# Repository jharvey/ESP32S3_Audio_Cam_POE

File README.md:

# ESP32S3_Audio_Cam_POE

This is a PCB layout for ESP32S3 with OV2640 / OV5640 camera. It was designed in KiCad 9 and converted to KiCad 10 (10.0.8); the files no longer open in KiCad 9.
The board's major features include:
* Camera.
* 2 way audio.
* Hardwired Ethernet including POE.
* Camera pan / tilt servos and lamp control.
* record to SD card.
* misc outputs to drive misc motors or similar outputs. 
* Battery powered option with Li-ion type of battery. 
* Stream video to NVR recording station. 

## Firmware
Firmware found here https://github.com/jharvey/ESP32-CAM_MJPEG2SD

Changes up to version 0.1:
* Initial layout
* Converted to KiCad 10.
* Removed the Medium and Smaller cost-reduction variants.

## Purpose

The layout design intent is to make a hardwired intercom system which includes options for camera, making a near equivalent of a doorbell camera. Hardwired means it's not susceptible to RF jamming, or similar attacks. It can be battery powered at the ethernet switch source so it can handle power outages. Lighting controls allow night time spot light, and day time spot light controls. Pan, Tilt, Rotate could potentially allow a laser pointer to distract bad players if things go bump in the night. 

## Installation
Clone with the JLCPCB library submodule, which the symbol and footprint tables point to:

```
git clone --recurse-submodules https://github.com/jharvey/ESP32S3_Audio_Cam_POE.git
```

All JLCPCB symbols, footprints and 3D models resolve from this submodule, so you do not need the JLCPCB library installed through the KiCad Plugin and Content Manager. Other 3D models use KiCad's standard `${KICAD10_3DMODEL_DIR}` library.

On Windows, if the submodule fails with "Filename too long" or "'$GIT_DIR' too big", enable long paths first (`git config --global core.longpaths true`) or clone to a shorter folder.

TBD currently has not had its first spin. TBD

## Layout status
The `single-sided` branch puts every assembled part on the top of a 4-layer board. Routing is in progress: see
[Docs/single_sided_layout.md](Docs/single_sided_layout.md) for the layout and
[Docs/routing_handoff.md](Docs/routing_handoff.md) for what is routed, what is open and how to continue.

## 3D case
See 3D case found here
TBD create file in OnShape and post link here. TBD

## 3D pictures from KICAD
<div align="center">

</div>

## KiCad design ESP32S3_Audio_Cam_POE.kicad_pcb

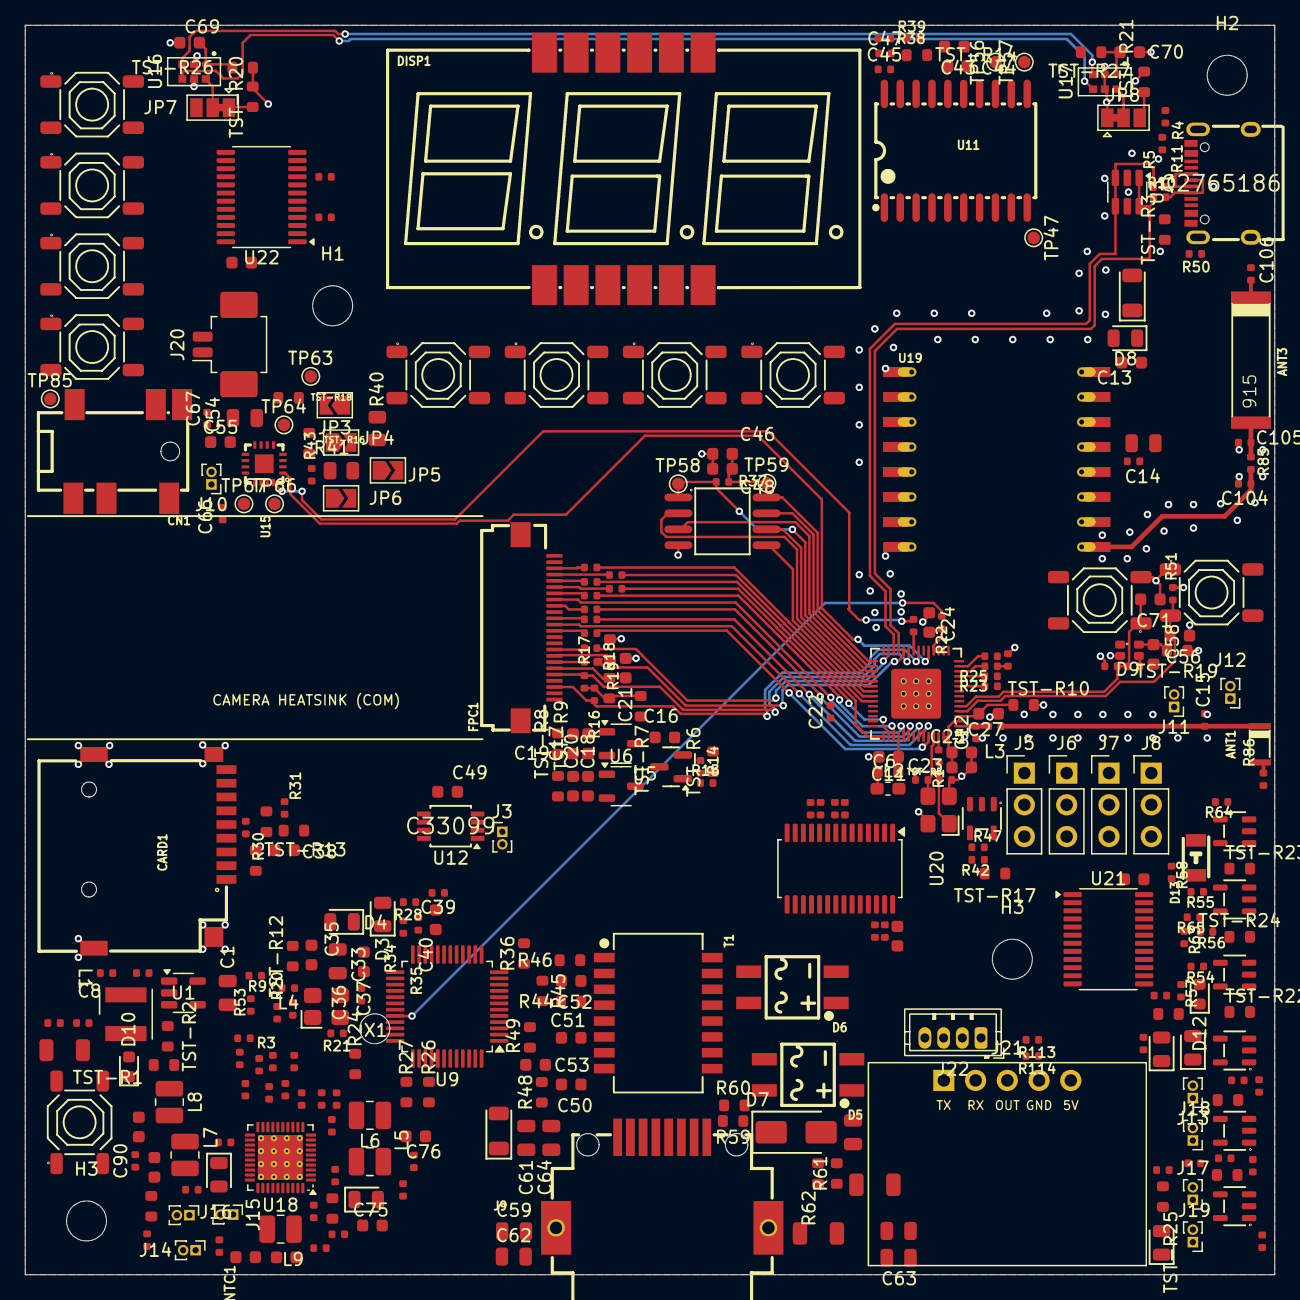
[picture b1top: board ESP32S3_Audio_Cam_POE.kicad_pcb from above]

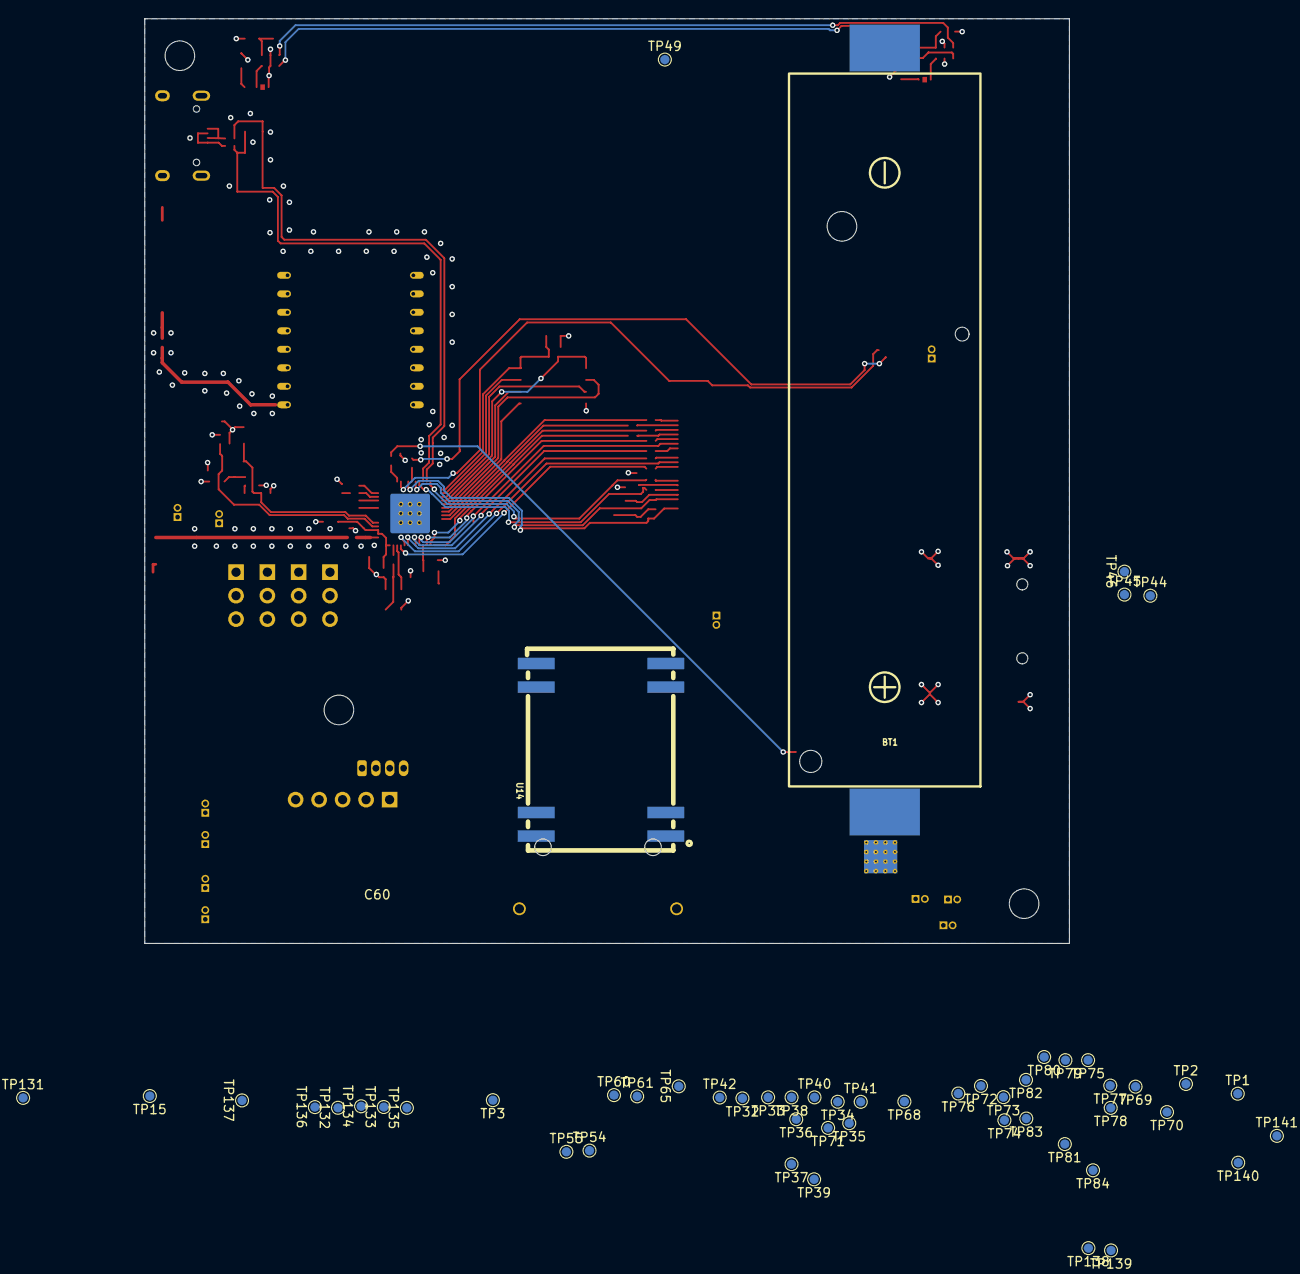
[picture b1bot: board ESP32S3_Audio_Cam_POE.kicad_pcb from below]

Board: 4 copper layers, 100.0 x 100.0 mm, 384 parts (54 on the bottom side), 275 nets.

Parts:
ANT1: KH-3216-H0209; ANT-SMD_L3.2-W1.6-KH-3216F245C04
ANT3: H2U646MHLQ0200; ANT-SMD_H2U646MHLQ0200
BOOT1: Tactile Button, 160gf; SW-SMD_4P-L5.1-W5.1-P3.70-LS6.5-TL-2
BT1: BH-18650-B1BA002; BATTERY-SMD_18650-1S-L77.1-W20.7-1
C1: 4.7uF; C_0805
C3, C6, C33, C34, C106: 10pF; C_0402
C8, C14, C74: 10uF; C_0402
C11, C13, C19, C20, C21, C24, C25, C27, C35, C37, C38, C44, C46, C49, C55, C56, C58, C69, C70, C71, C100, C108, C109: 100nF; C_0603
C12, C105: 3.3pF; C_0402
C15: 1pF; C_0402
C16, C17, C18, C23, C43, C48: 1uF; C_0603
C22: 15pF; C_0402
C36, C54, C61, C103: 10uF; C_0805
C39: 10nF; C_0402
C40: 4.7uF; C_0603
C45, C47: 100pF; C_0402
C50, C51: 6.8nF; C_0603
C52, C53: 220nF; C_0603
C59, C60, C62, C63, C107: 100nF; C_0805
C64: 22uF; C_0805
C65, C68: 1nF; C_1206
C66, C67: 220pF; C_0402
C73, C88, C90, C91, C92, C93, C94: 1uF; C_0402
C75, C76, C77, C78, C95, C97: 22uF; C_0603
C79, C80, C81, C82, C83, C84, C85, C86, C87, C96: 2.2uF; C_0402
C89: 4.7uF; C_0402
C104: 4.7pF; C_0402
CARD1: TF PUSH; TF-PUSH-SD-CARD_C393941
CN1: PJ-316C-6A; SMD_3.5mm_Audio_Connectors_(Headphones)_C707223
D1, D11: DSK24; D_SOD-123FL
D3: Yellow; D_0805
D4, D8, D15, D16, D17, D18: Green; D_0805
D5, D6: MB6S; MB6S-C82584
D7: SMAJ58A; D_SMA
D9: WS2812B; LED-SMD_4P-L1.6-W1.5_XL-1615RGBC-WS2812B
D10: Red; D_0603
D12: White; D_0603
D13: IR; IR-LED_C131280
D14: Blue; D_0805
DISP1: SLS0563DBA1GD; 3x7-seg_LED-RED_C2913084
FPC1: AFC01-S24FCC-00; OV2640_connector_AFC01-S24FCC-00
H1, H2, H3, H3#2: M3; MountingHole_3.2mm_M3
J1: Connector, USB-TYPE-C-16P; USB-C-SMD_TYPE-C-16PIN-2MD-073
J3, J10, J11, J12, J13, J14, J15, J16, J17, J18, J19: Conn_01x02; PinHeader_1x02_P1.00mm_Vertical
J5, J6, J7, J8: Conn_01x03; PinHeader_1x03_P2.54mm_Vertical
J9: HC-RJ45-055-4_8P8C_Shielded; HC-RJ45-055-4_C3000211
J20: 53261-0271; Molex_PicoBlade_53261-0271_1x02-1MP_P1.25mm_Horizontal
J21: HLK-LD2410C
J22: HLK-LD2450 cable; JST_ZH_B4B-ZR_1x04_P1.50mm_Vertical
JP3, JP4, JP5, JP6: SolderJumper_2_Open; SolderJumper-2_P1.3mm_Open_TrianglePad1.0x1.5mm
JP7, JP8: SolderJumper_3_Bridged12; SolderJumper-3_P1.3mm_Bridged12_Pad1.0x1.5mm
L1: 2.2uH; L_Wurth_WE-LQSH-4020
L2: 2nH; L_0603_1608Metric_Pad1.05x0.95mm_HandSolder
L3, L4: 3.9nH,300mA; L_0402
L5, L6, L7, L8, L9: 1uH,3.3A; L_1008_2520Metric
NTC1: NTC; R_0402
PB1, PB2, PB3, PB4, PB5, PB7, PB10, PB11, PB12: Tactile Button, 160gf; SW-SMD_4P-L5.1-W5.1-P3.70-LS6.5-TL-2
Q1: AO3401A; Q_SOT-23
Q2, Q3, Q4, Q5, Q6, Q7, Q8: SY6288AAAC; SOT-23-5_L3.0-W1.7-P0.95-LS2.8-BL
R1, R3, R22, R23, R25: 22Ω; R_0402
R4, R5: 5.1kΩ; R_0402
R8, R9, R37, R42, R54, R55, R56, R79, R82, R101: 100kΩ; R_0402
R10, R11, R88, R89, R90, R91, R92, R93, R94, R95, R96, R97, R98, R99, R100, R110: 33Ω; R_0402
R14: 10MΩ; R_0402
R15, R20, R43: 1MΩ; R_0402
R16, R17, R28, R30, R31, R38, R39, R50, R51, R53, R64, R65, R67, R75, R78, R81, R84, R109: 10kΩ; R_0402
R18, R19: 10kΩ; R_0603
R21, R85, R86, R113, R114: 0Ω; R_0402
R24, R26, R27: 20Ω; R_0603
R29, R32, R36: 12kΩ; R_0603
R34, R35: 680Ω; R_0402
R40, R41: 100kΩ; R_0805
R44, R45, R46: 47Ω; R_0603
R47, R57, R58, R63, R66, R77, R80, R83, R111, R112: 1kΩ; R_0402
R48, R49: 82Ω; R_0603
R59, R60, R61, R62: 75Ω; R_0603
R74, R76: 220kΩ; R_0402
R102, R103, R104, R105, R106, R107: 4.7kΩ; R_0402
R108: 0Ω; R_1206
RST2: Tactile Button, 160gf; SW-SMD_4P-L5.1-W5.1-P3.70-LS6.5-TL-2
T1: H1102NLT; H1102NLT_C18584
TP1, TP2, TP3, TP15, TP32, TP33, TP34, TP35, TP36, TP37, TP38, TP39, TP40, TP41, TP42, TP44, TP45, TP46, TP47, TP49, TP54, TP55, TP56, TP57, TP58, TP59, TP60, TP61, TP63, TP64, TP65, TP66, TP67, TP68, TP69, TP70, TP71, TP72, TP73, TP74, TP75, TP76, TP77, TP78, TP79, TP80, TP81, TP82, TP83, TP84, TP85, TP131, TP132, TP133, TP134, TP135, TP136, TP137, TP138, TP139, TP140, TP141: TestPoint; TestPoint_Pad_D1.0mm
TST-R1, TST-R2, TST-R3, TST-R5, TST-R6, TST-R7, TST-R8, TST-R9, TST-R10, TST-R12, TST-R13, TST-R14, TST-R16, TST-R17, TST-R18, TST-R19, TST-R20, TST-R21, TST-R22, TST-R23, TST-R24, TST-R25, TST-R26, TST-R27, TST-R28, TST-R29, TST-R30, TST-R31, TST-R32: 0Ω; R_0603
U1: TLV62568DBVR; SOT-23-5
U3: USBLC6-2SC6; SOT-23-6
U5: XC6206-1.5NR; SOT-23-3
U6: XC6206-2.8V; SOT-23-3
U7: ESP32-S3; QFN-56-1EP_7x7mm_P0.4mm_EP4x4mm_ThermalVias
U9: W5500; LQFP-48_7x7mm_P0.5mm
U11: TM1637; digital tube drivers_c2962580
U12: LM75BDP,118; TSSOP-8_3x3mm_P0.65mm
U13: W25Q128JVSIQ; SOIC-8_L5.3-W5.3-P1.27-LS8.0-BL
U14: DP9900M-5V; DP9900M_C5380106
U15: MAX98357AETE+T; MAX98357AETE+T_C910544
U16, U17: MSM261DGT003; LGA-6_2.0x4.0mm_MSM261DGT003
U18: AXP2101; QFN-40-1EP_5x5mm_P0.4mm_EP3.6x3.6mm_ThermalVias
U19: DL-RFM95-915M; RFM69HCW
U20: PCA9685PW; TSSOP-28_4.4x9.7mm_P0.65mm
U21, U22: TCA9555PWR; TSSOP-24_4.4x7.8mm_P0.65mm
X1: X322525MOB4SI; OSC-SMD_4P-L3.2-W2.5-BL
Y1: 40MHz, 15pF; OSC-SMD_4P-L3.2-W2.5-BL_SIT8008BI

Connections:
+1V5: FPC1.10 (10_1V2), TST-R8.2
+2V8: FPC1.4 (4_2V8), FPC1.11 (11_2V8), TST-R9.2
+3V3: C13.2, C14.1, C49.2, C100.1, C103.1, C108.1, C109.2, D3.2, D4.2, L2.2, R51.2, R53.2, R102.1, R103.1, R104.1, R105.1, R106.1, R107.1, R109.2, TST-R2.2, TST-R6.2, TST-R7.1, TST-R10.2, TST-R12.2, TST-R13.2, TST-R14.2, TST-R19.2, TST-R20.2, TST-R21.2, TST-R26.2, TST-R27.2, TST-R29.2, U12.8 (+Vs), U19.5 (VDD), U20.28 (VDD), U21.24 (VCC), U22.21 (A0), U22.24 (VCC)
+3V3A: C36.2, C37.2, L4.1, R44.2, R45.2, R46.2, U9.4 (AVDD), U9.8 (AVDD), U9.11 (AVDD), U9.15 (AVDD), U9.17 (AVDD), U9.21 (AVDD), U9.28 (VDD)
+3V3_RF: C11.2, TST-R5.1, U7.46 (VDD3P3_CPU)
/3V3-U16: C69.1, TST-R26.1, U16.1 (VDD)
/3V3-U17: C70.1, TST-R27.1, U17.1 (VDD)
/7SEG.GRID1: DISP1.12 (DIG1), U11.15 (GRID1)
/7SEG.GRID2: DISP1.8 (DIG2), U11.14 (GRID2)
/7SEG.GRID3: DISP1.7 (DIG3), U11.13 (GRID3)
/7SEG.SEG1: DISP1.9 (A), U11.2 (SEG1/KS1)
/7SEG.SEG2: DISP1.5 (B), U11.3 (SEG2/KS2)
/7SEG.SEG3: DISP1.4 (C), U11.4 (SEG3/KS3)
/7SEG.SEG4: DISP1.3 (D), U11.5 (SEG4/KS4)
/7SEG.SEG5: DISP1.1 (E), U11.6 (SEG5/KS5)
/7SEG.SEG6: DISP1.10 (F), U11.7 (SEG6/KS6)
/7SEG.SEG7: DISP1.2 (G), U11.8 (SEG7/KS7)
/7SEG.SEG8: DISP1.6 (DP), U11.9 (SEG8/KS8)
/BTN.DOWN: PB5.4 (D), U22.7 (P03)
/BTN.MODE: PB2.4 (D), U22.5 (P01)
/BTN.OFFICE: R112.1, U22.9 (P05)
/BTN.OFFICE_SW: PB7.4 (D), R112.2
/BTN.TALK1: R111.1, U22.4 (P00)
/BTN.TALK1_SW: PB1.4 (D), R111.2
/BTN.TALK10: PB10.4 (D), U22.13 (P10)
/BTN.TALK11: PB11.4 (D), U22.14 (P11)
/BTN.TALK12: PB12.4 (D), U22.15 (P12)
/BTN.UP: PB4.4 (D), U22.6 (P02)
/CAM.D0: R92.1, U7.44 (MTCK)
/CAM.D1: R94.1, U7.37 (SPICLK_P)
/CAM.D2: R95.1, U7.36 (SPICLK_N)
/CAM.D3: R93.1, U7.43 (GPIO38)
/CAM.D4: R91.1, U7.45 (MTDO)
/CAM.D5: R90.1, U7.48 (MTMS)
/CAM.D6: R89.1, U7.50 (U0RXD)
/CAM.D7: R88.1, U7.52 (GPIO46)
/CAM.HREF: R98.1, U7.27 (GPIO21)
/CAM.MCLK: FPC1.13 (13_MCLK), U7.51 (GPIO45)
/CAM.PCLK: C22.2, FPC1.17 (17_PCLK), U7.47 (MTDI)
/CAM.PWDN: FPC1.8 (8_PWDN), R19.2
/CAM.PWR: R15.2, U21.8 (P04)
/CAM.RST: C21.2, FPC1.6 (6_RST), R18.2
/CAM.SCL: FPC1.5 (5_SCL-SIO-CLK), R17.2, U7.23 (GPIO17)
/CAM.SDA: FPC1.3 (3_SDA-SIO-DAT), R16.2, U7.21 (XTAL_32K_P)
/CAM.VSYNC: R97.1, U7.24 (GPIO18)
/CHIP_BOOT: BOOT1.1 (A), C71.2, R109.1, R110.1, U7.5 (GPIO0)
/CHIP_PU: C56.2, R51.1, RST2.3 (C), U7.4 (CHIP_PU)
/CK_XTAL1: R21.2, U9.30 (XI/CLKIN)
/CK_XTAL2: C33.1, R20.1, U9.31 (XO), X1.1 (OSC)
/ESP.I2S.WS: R100.1, U7.13 (GPIO8)
/ESP.MIC.SCK: R96.1, U7.22 (XTAL_32K_N)
/ESP.MIC.SD: R99.1, U7.12 (GPIO7)
/ETH.CS: R22.1, U7.18 (GPIO13)
/ETH.INT_EXP: R26.1, U21.7 (P03)
/ETH.MISO: R24.1, U7.10 (GPIO5), U19.10 (MISO)
/ETH.MOSI: R25.1, U7.11 (GPIO6), U19.11 (MOSI)
/ETH.RST_EXP: R27.1, U21.6 (P02)
/ETH.SCLK: R23.1, U7.9 (GPIO4), U19.12 (SCK)
/EXP.INT: U21.1 (~INT), U22.1 (~INT)
/FGND1: C59.2, C60.1, C62.2, C63.1, C65.1, J9.9 (SH), J9.10 (SH)
/FLASH_QSPI_CLK: U7.33 (SPICLK), U13.6 (CLK)
/FLASH_QSPI_DI: U7.35 (SPID), U13.5 (DI)
/FLASH_QSPI_DO: U7.34 (SPIQ), U13.2 (DO)
/FLASH_QSPI_nCS: R37.1, TP58.1 (1_1), U7.32 (SPICS0), U13.1 (CS#)
/FLASH_QSPI_nH: U7.30 (SPIHD), U13.7 (IO3)
/FLASH_QSPI_nWP: U7.31 (SPIWP), U13.3 (IO2)
/FLT.IR: Q4.3 (OCB), U21.14 (P11)
/FLT.M1: Q6.3 (OCB), U21.16 (P13)
/FLT.M2: Q7.3 (OCB), U21.17 (P14)
/FLT.M3: Q8.3 (OCB), U21.18 (P15)
/FLT.OTH: Q5.3 (OCB), U21.15 (P12)
/FLT.RC: Q2.3 (OCB), U21.19 (P16)
/FLT.WH: Q3.3 (OCB), U21.13 (P10)
/I2C.SCL: J3.1, R102.2, U7.49 (U0TXD), U12.2 (SCL), U18.39 (SCK), U20.26 (SCL), U21.22 (SCL), U22.22 (SCL)
/I2C.SDA: J3.2, R103.2, U7.17 (GPIO12), U12.1 (SDA), U18.40 (SDA), U20.27 (SDA), U21.23 (SDA), U22.23 (SDA)
/I2S.SCK: R96.2, U15.16 (BCLK)
/I2S.WS: R100.2, U15.14 (LRCLK)
/LED.DIN: D9.4 (DIN), R110.2
/LED.IR: R58.2, U20.21 (LED14)
/LED.OTH: R63.2, U20.19 (LED12)
/LED.VDD: C58.2, D9.2 (VDD), TST-R19.1
/LED.WH: R57.2, U20.18 (LED11)
/LORA1: C104.1, R85.1, U19.1 (ANT)
/LORA1-ANT: ANT3.1 (ANT), C105.1, R85.2
/LORA_CS: U7.16 (GPIO11), U19.13 (NSS)
/LORA_IRQ: U19.6 (DIO0), U22.17 (P14)
/LORA_RST: U19.14 (RESET), U21.9 (P05)
/MIC.CLK: U7.14 (GPIO9), U16.4 (CLK), U17.4 (CLK)
/MIC.L: JP8.2 (C), U17.6 (L/R)
/MIC.R: JP7.2 (C), U16.6 (L/R)
/MIC.SD: R99.2, R101.1, U16.3 (DATA), U17.3 (DATA)
/MISC.OUT1: R77.2, U20.15 (LED8)
/MISC.OUT2: R80.2, U20.16 (LED9)
/MISC.OUT3: R83.2, U20.17 (LED10)
/OSC_IN: R1.2, U7.54 (XTAL_P)
/OSC_OUT: C6.1, U7.53 (XTAL_N), Y1.3 (OSC)
/PMU.IRQ: U18.38 (IRQ), U21.5 (P01)
/PMU.Va1: C79.2, U18.18 (ALDO1)
/PMU.Va2: C82.2, U18.19 (ALDO2)
/PMU.Va3: C80.2, U18.16 (ALDO3)
/PMU.Va4: C81.2, U18.15 (ALDO4)
/PMU.Vb1: C84.2, U18.12 (BLDO1)
/PMU.Vb2: C85.2, U18.14 (BLDO2)
/PMU.Vcpu: C86.2, U18.10 (CPULDOS)
/PMU.Vd1: C83.2, U18.20 (DLDO1/DC1SW)
/PMU.Vd2: C87.2, U18.11 (DLDO2/DC4SW)
/PMU.Vo1: C78.2, L8.1, TST-R29.1, U18.22 (LX1)
/PMU.Vo2: C77.2, L7.1, U18.26 (FB2)
/PMU.Vo3: C75.2, L5.1, U18.4 (FB3)
/PMU.Vo4: C76.2, L6.1, U18.8 (LX4)
/PMU.Vref: C73.2, U18.2 (VREF)
/PMU.Vsys: C88.2, C89.2, C91.2, C92.2, C93.2, C94.2, R66.2, R67.2, U18.6 (VIN3), U18.7 (VIN4), U18.13 (BLDOIN), U18.17 (ALDOIN), U18.23 (VIN1), U18.24 (VIN2), U18.34 (VSYS), U18.36 (VMID)
/POE_5V: C61.1, C64.1, D11.2, U14.1 (+VDC), U14.2 (+VDC)
/PWM.OE: U20.23 (~OE), U21.4 (P00)
/RADAR.OUT: J21.3, U22.16 (P13)
/RADAR.TX: J22.3, R113.1, U7.15 (GPIO10)
/RC.OTHR: J8.1, R107.2, U20.11 (LED5)
/RC.PAN: J5.1, R104.2, U20.7 (LED1)
/RC.PWR: R47.2, U20.22 (LED15)
/RC.ROT: J7.1, R106.2, U20.10 (LED4)
/RC.TILT: J6.1, R105.2, U20.8 (LED2)
/RC.VDD: J5.2, J6.2, J7.2, J8.2, Q2.1 (OUT)
/RF1: C12.1, L3.1, U7.1 (LNA_IN)
/RF1-ANT: ANT1.1 (ANT), C15.1, L3.2
/SD.CLK: CARD1.5 (CLX), R31.2, U7.7 (GPIO2)
/SD.CS: CARD1.2 (CD/DAT3), R29.2
/SD.MISO: CARD1.7 (DAT0), R32.2, U7.6 (GPIO1)
/SD.MOSI: CARD1.3 (CMD), R30.2, U7.8 (GPIO3)
/SPK.DIN: U7.19 (GPIO14), U15.1 (DIN)
/SPK.MIC: CN1.4, TP85.1 (1_1)
/SPK.MODE: R43.2, U15.4 (SD_MODE#)
/SPK.OutN: C66.2, CN1.1, J10.2, J20.2, U15.10 (OUTN)
/SPK.OutP: C67.1, CN1.2, CN1.3, U15.9 (OUTP)
/SPK.OutPS: CN1.5, CN1.6, J10.1, J20.1
/TM.CLK: C45.2, R38.1, U11.18 (CLK), U21.10 (P06)
/TM.DIO: C47.2, R39.1, U11.17 (DIO), U21.11 (P07)
/USB_CC1: J1.A5 (CC1), R4.1
/USB_CC2: J1.B5 (CC2), R5.1
/USB_D+: R11.2, U3.3 (I/O2), U3.4 (I/O2), U7.26 (GPIO20/USB_D+)
/USB_D-: R10.2, U3.1 (I/O1), U3.6 (I/O1), U7.25 (GPIO19/USB_D-)
/USB_PRT_D+: J1.A6 (D+), J1.B6 (D+), R11.1
/USB_PRT_D-: J1.A7 (D-), J1.B7 (D-), R10.1
/VDCDC5: C95.2, C97.2, L9.1, U18.32 (GPIO1/FB5/RTC/LDO2)
/W_BR_N: C107.2, D5.2 (-), D6.2 (-), D7.2, U14.7 (VIN-), U14.8 (VIN-)
/W_BR_P: C107.1, D5.1 (+), D6.1 (+), D7.1, U14.5 (VIN+), U14.6 (VIN+)
/W_RD_N: J9.6, T1.9
/W_RD_OUT_N: C50.2, R48.1, U9.5 (RXN)
/W_RD_OUT_P: C51.2, R49.1, U9.6 (RXP)
/W_RD_P: J9.3, T1.11
/W_RXCM: D6.4, T1.10
/W_TD_N: J9.2, T1.14
/W_TD_OUT_N: R44.1, T1.3, U9.1 (TXN)
/W_TD_OUT_P: R46.1, T1.1, U9.2 (TXP)
/W_TD_P: J9.1, T1.16
/W_TERM: C65.2, R59.1, R60.1, R61.1, R62.1
/W_TERM2: C68.1, R61.2, R62.2
/W_TXCM: D6.3, T1.15
/W_VN: D5.3, J9.7, J9.8, R59.2
/W_VP: D5.4, J9.4, J9.5, R60.2
COM: BOOT1.3 (C), BT1.1, C1.2, C3.2, C6.2, C8.2, C11.1, C12.2, C13.1, C14.2, C15.2, C16.2, C17.2, C18.2, C19.1, C20.1, C21.1, C22.1, C23.1, C24.2, C25.2, C27.2, C33.2, C34.1, C35.1, C36.1, C37.1, C38.1, C39.2, C40.2, C43.1, C44.2, C45.1, C46.1, C47.1, C48.2, C49.1, C52.2, C53.2, C54.2, C55.2, C56.1, C58.1, C59.1, C60.2, C61.2, C62.1, C63.2, C64.2, C66.1, C67.2, C68.2, C69.2, C70.2, C71.1, C73.1, C74.2, C75.1, C76.1, C77.1, C78.1, C79.1, C80.1, C81.1, C82.1, C83.1, C84.1, C85.1, C86.1, C87.1, C88.1, C89.1, C90.1, C91.1, C92.1, C93.1, C94.1, C95.1, C96.1, C97.1, C100.2, C103.2, C104.2, C105.2, C106.1, C108.2, C109.1, CARD1.6 (VSS), CARD1.10, CARD1.11, CARD1.12, CARD1.13, D8.1, D9.3 (GND), D10.1, D12.1, D13.1 (C), D16.1, D17.1, D18.1, FPC1.2 (2_GND), FPC1.15 (15_GND), J1.A12B1 (GND), J1.B12A1 (GND), J1.S1 (SHIELD), J5.3, J6.3, J7.3, J8.3, J11.2, J12.2, J13.2, J14.2, J15.2, J16.2, J17.2, J18.2, J19.2, J21.4, J22.4, JP5.1 (A), JP7.3 (B), JP8.1 (A), NTC1.1, PB1.2 (B), PB2.2 (B), PB3.3 (C), PB4.2 (B), PB5.2 (B), PB7.2 (B), PB10.2 (B), PB11.2 (B), PB12.2 (B), Q2.2 (GND), Q3.2 (GND), Q4.2 (GND), Q5.2 (GND), Q6.2 (GND), Q7.2 (GND), Q8.2 (GND), R4.2, R5.2, R9.2, R19.1, R28.2, R36.2, R41.1, R86.2, R101.2, RST2.1 (A), TST-R17.2, TST-R22.2, TST-R23.2, TST-R24.1, TST-R30.2, TST-R31.2, TST-R32.2, U1.2 (GND), U3.2 (GND), U5.1 (GND), U6.1 (GND), U7.57 (GND), U9.3 (AGND), U9.9 (AGND), U9.14 (AGND), U9.16 (AGND), U9.19 (AGND), U9.29 (GND), U9.48 (AGND), U11.1 (GND), U12.4 (GND), U12.5 (A2), U12.6 (A1), U12.7 (A0), U13.4 (GND), U14.3 (-VDC), U15.3 (GND), U15.11 (GND), U15.15 (GND), U15.17 (EP), U16.2 (GND), U16.5 (GND), U17.2 (GND), U17.5 (GND), U18.3 (GND), U18.41 (EP), U19.2 (GND@1), U19.9 (GND@2), U19.16 (GND@3), U20.1 (A0), U20.2 (A1), U20.3 (A2), U20.4 (A3), U20.5 (A4), U20.14 (VSS), U20.24 (A5), U20.25 (EXTCLK), U21.2 (A1), U21.3 (A2), U21.12 (GND), U21.21 (A0), U22.2 (A1), U22.3 (A2), U22.12 (GND), X1.2 (GND), X1.4 (GND), Y1.2 (GND), Y1.4 (GND)
unnamed: ANT1.2, R86.1
unnamed: ANT3.2, C106.2
unnamed: C3.1, R1.1, Y1.1 (OSC)
unnamed: C8.1, L1.2, R76.1, TST-R2.1
unnamed: C34.2, R20.2, R21.1, X1.3 (OSC)
unnamed: C35.2, L4.2, TST-R12.1
unnamed: C50.1, T1.8
unnamed: C51.1, T1.6
unnamed: C52.1, R45.1, T1.2
unnamed: C53.1, R48.2, R49.2, T1.7
unnamed: C54.1, C55.1, TST-R18.1, U15.7 (VDD), U15.8 (VDD)
unnamed: C38.2, CARD1.4 (VDD), R29.1, R30.1, R31.1, R32.1, TST-R13.1
unnamed: D1.2, J1.A9B4 (VBUS), J1.B9A4 (VBUS)
unnamed: D3.1, R34.2
unnamed: D4.1, R35.2
unnamed: D8.2, R50.1
unnamed: D10.2, R53.1
unnamed: D11.1, TST-R25.1
unnamed: D12.2, R65.2
unnamed: D13.2 (A), R64.2
unnamed: D14.2, R66.1
unnamed: D15.2, R67.1
unnamed: D16.2, R78.2
unnamed: D17.2, R81.2
unnamed: D18.2, R84.2
unnamed: DISP1.11 (NC), TP49.1 (1_1)
unnamed: FPC1.7 (7_VSYNC), R97.2
unnamed: FPC1.9 (9_HREF), R98.2
unnamed: FPC1.12 (12_Y9-D7), R88.2
unnamed: FPC1.14 (14_Y8-D6), R89.2
unnamed: FPC1.16 (16_Y7-D5), R90.2
unnamed: FPC1.18 (18_Y6-D4), R91.2
unnamed: FPC1.19 (19_Y2-D0), R92.2
unnamed: FPC1.20 (20_Y5-D3), R93.2
unnamed: FPC1.21 (21_Y3-D1), R94.2
unnamed: FPC1.22 (22_Y4-D2), R95.2
unnamed: J11.1, Q5.1 (OUT)
unnamed: J12.1, Q4.1 (OUT), R64.1
unnamed: J13.1, Q3.1 (OUT), R65.1
unnamed: BT1.2, C96.2, J14.1, U18.33 (BAT)
unnamed: J15.1, U18.27 (VBACKUP)
unnamed: J16.1, NTC1.2, U18.31 (TS)
unnamed: J17.1, Q6.1 (OUT), R78.1
unnamed: J18.1, Q7.1 (OUT), R81.1
unnamed: J19.1, Q8.1 (OUT), R84.1
unnamed: J21.1, R113.2
unnamed: J21.5, R114.2
unnamed: JP3.2 (B), JP4.2 (B), JP5.2 (B), JP6.2 (B), U15.2 (GAIN_SLOT)
unnamed: JP4.1 (A), R40.2
unnamed: JP6.1 (A), R41.2
unnamed: JP7.1 (A), TST-R20.1
unnamed: JP8.3 (B), TST-R21.1
unnamed: L2.1, TST-R5.2
unnamed: PB3.1 (A), U18.30 (PWRON)
unnamed: C16.1, Q1.3 (D), U5.3 (VI), U6.3 (VI)
unnamed: Q1.1 (G), R14.2, R15.1
unnamed: Q1.2 (S), R14.1, TST-R6.1
unnamed: Q2.4 (EN), R42.2, R47.1
unnamed: Q3.4 (EN), R54.2, R57.1
unnamed: Q4.4 (EN), R55.2, R58.1
unnamed: Q5.4 (EN), R56.2, R63.1
unnamed: Q6.4 (EN), R8.2, R77.1
unnamed: Q7.4 (EN), R79.2, R80.1
unnamed: Q8.4 (EN), R82.2, R83.1
unnamed: R8.1, TST-R30.1
unnamed: R16.1, R17.1, R18.1, TST-R7.2
unnamed: R28.1, U9.23 (RSVD)
unnamed: R42.1, TST-R17.1
unnamed: R43.1, TST-R16.2
unnamed: R54.1, TST-R22.1
unnamed: R55.1, TST-R23.1
unnamed: R56.1, TST-R24.2
unnamed: R74.1, R75.1
unnamed: R74.2, R76.2
unnamed: R79.1, TST-R31.1
unnamed: R82.1, TST-R32.1
unnamed: TP63.1 (1_1), U15.5 (N.C.)
unnamed: TP64.1 (1_1), U15.6 (N.C.)
unnamed: TP66.1 (1_1), U15.13 (N.C.)
unnamed: TP67.1 (1_1), U15.12 (N.C.)
unnamed: R3.2, U1.1 (EN)
unnamed: R9.1, R75.2, U1.5 (FB)
unnamed: L1.1, U1.3 (SW)
unnamed: C1.1, R3.1, TST-R1.2, U1.4 (VIN)
unnamed: TST-R3.2, U3.5 (VBUS)
unnamed: C17.1, C19.2, TST-R8.1, U5.2 (VO)
unnamed: C18.1, C20.2, TST-R9.1, U6.2 (VO)
unnamed: C23.2, C24.1, C25.1, C27.1, TST-R10.1, U7.2 (VDD3P3), U7.3 (VDD3P3), U7.20 (VDD3P3_RTC), U7.55 (VDDA), U7.56 (VDDA)
unnamed: C39.1, U9.22 (1V2O)
unnamed: R35.1, U9.27 (ACTLED)
unnamed: R36.1, U9.10 (EXRES1)
unnamed: R34.1, U9.25 (LINKLED)
unnamed: R24.2, U9.34 (MISO)
unnamed: R25.2, U9.35 (MOSI)
unnamed: R23.2, U9.33 (SCLK)
unnamed: C40.1, U9.20 (TOCAP)
unnamed: R26.2, U9.36 (~INT)
unnamed: R27.2, U9.37 (~RST)
unnamed: R22.2, U9.32 (~SCS)
unnamed: TP56.1 (1_1), U11.12 (GRID4)
unnamed: TP57.1 (1_1), U11.11 (GRID5)
unnamed: TP47.1 (1_1), U11.10 (GRID6)
unnamed: C43.2, C44.1, R38.2, R39.2, TST-R14.1, U11.16 (VDD)
unnamed: D14.1, U18.1 (CHGLED)
unnamed: L8.2, U18.21 (FB1)
unnamed: L6.2, U18.9 (FB4)
unnamed: L7.2, U18.25 (LX2)
unnamed: L5.2, U18.5 (LX3)
unnamed: D15.1, U18.29 (PWROK)
unnamed: L9.2, U18.35 (SW)
unnamed: C74.1, TST-R28.1, U18.37 (VBUS)
unnamed: C90.2, U18.28 (VRTC)
VBUS: D1.1, J22.1, R50.2, R108.1, R114.1, TST-R3.1, TST-R25.2
VDD_SPI: C46.2, C48.1, R37.2, TP59.1 (1_1), U7.29 (VDD_SPI), U13.8 (VCC)
Vdrive: JP3.1 (A), Q2.5 (IN), Q3.5 (IN), Q4.5 (IN), Q5.5 (IN), Q6.5 (IN), Q7.5 (IN), Q8.5 (IN), R40.1, R108.2, TST-R1.1, TST-R16.1, TST-R18.2, TST-R28.2

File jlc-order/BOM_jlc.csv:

Comment,Designator,Footprint,LCSC
KH-3216-H0209,ANT1,ANT-SMD_L3.2-W1.6-KH-3216F245C04,C2925417
H2U646MHLQ0200,ANT3,ANT-SMD_H2U646MHLQ0200,C5370061
4.7uF,C1,C_0805,C1779
4.7pF,C104,C_0402,C1569
100nF,"C100,C108,C109,C11,C13,C19,C20,C21,C24,C25,C27,C30,C35,C37,C38,C44,C46,C49,C55,C56,C58,C68,C69,C70",C_0603,C14663
1pF,C15,C_0402,C1550
1uF,"C16,C17,C18,C23,C43,C48",C_0603,C15849
15pF,C22,C_0402,C1548
10pF,"C106,C3,C33,C34,C6",C_0402,C32949
10nF,C39,C_0402,C15195
4.7uF,C40,C_0603,C19666
100pF,"C45,C47",C_0402,C1546
6.8nF,"C50,C51",C_0603,C1631
220nF,"C52,C53",C_0603,C21120
100nF,"C107,C59,C60,C62,C63",C_0805,C28233
10uF,"C103,C36,C54,C61",C_0805,C440198
22uF,C64,C_0805,C45783
1nF,C65,C_1206,C9196
220pF,"C66,C67",C_0402,C1530
10uF,"C14,C74,C8",C_0402,C15525
22uF,"C75,C76,C77,C78,C95,C97",C_0603,C59461
2.2uF,"C79,C80,C81,C82,C83,C84,C85,C86,C87,C96",C_0402,C12530
4.7uF,C89,C_0402,C23733
1uF,"C73,C88,C90,C91,C92,C93,C94",C_0402,C52923
TF PUSH,CARD1,TF-PUSH-SD-CARD_C393941,C393941
PJ-316C-6A,CN1,SMD_3.5mm_Audio_Connectors_(Headphones)_C707223,C707223
DSK24,"D1,D11",D_SOD-123FL,C22466352
Red,D10,D_0603,C2286
White,D12,D_0603,C2290
IR,D13,IR-LED_C131280,C131280
Blue,D14,D_0805,C2293
Green,"D15,D16,D17,D18,D4,D8",D_0805,C2297
Yellow,D3,D_0805,C2296
MB6S,"D5,D6",MB6S-C82584,C82584
SMAJ58A,D7,D_SMA,C19077554
WS2812B,D9,LED-SMD_4P-L1.6-W1.5_XL-1615RGBC-WS2812B,C5349954
SLS0563DBA1GD,DISP1,3x7-seg_LED-RED_C2913084,C2913085
AFC01-S24FCC-00,FPC1,OV2640_connector_AFC01-S24FCC-00,C262276
"Connector, USB-TYPE-C-16P",J1,USB-C-SMD_TYPE-C-16PIN-2MD-073,C2765186
53261-0271,J20,Molex_PicoBlade_53261-0271_1x02-1MP_P1.25mm_Horizontal,C177225
2.2uH,L1,L_Wurth_WE-LQSH-4020,C135262
2nH,L2,L_0603_1608Metric_Pad1.05x0.95mm_HandSolder,C29682
"3.9nH,300mA","L3,L4",L_0402,C14033
"1uH,3.3A","L5,L6,L7,L8,L9",L_1008_2520Metric,C435392
NTC,NTC1,R_0402,C3018545
"Tactile Button, 160gf","BOOT1,PB1,PB10,PB11,PB12,PB2,PB3,PB4,PB5,PB7,RST2",SW-SMD_4P-L5.1-W5.1-P3.70-LS6.5-TL-2,C318884
AO3401A,Q1,Q_SOT-23,C15127
SY6288AAAC,"Q2,Q3,Q4,Q5,Q6,Q7,Q8",SOT-23-5_L3.0-W1.7-P0.95-LS2.8-BL,C111829
22Ω,"R1,R3",R_0402,C25092
4.7kΩ,"R102,R103,R104,R105,R106,R107",R_0402,C25900
0Ω,R108,R_1206,C17888
10MΩ,R14,R_0402,C26082
0Ω,"R21,R85,R86",R_0402,C17168
20Ω,"R22,R23,R24,R25,R26,R27",R_0603,C22950
10kΩ,"R109,R16,R17,R18,R19,R28,R30,R31,R38,R39,R50,R51,R53,R64,R65,R67,R75,R78,R81,R84",R_0402,C25744
12kΩ,"R29,R32,R36",R_0603,C22790
680Ω,"R34,R35",R_0402,C25130
100kΩ,"R101,R37,R42,R54,R55,R56,R79,R8,R82,R9",R_0402,C25741
100kΩ,"R40,R41",R_0805,C149504
1MΩ,"R15,R20,R43",R_0402,C26083
47Ω,"R44,R45,R46",R_0603,C23182
1kΩ,"R111,R112,R47,R57,R58,R63,R66,R77,R80,R83",R_0402,C11702
82Ω,"R48,R49",R_0603,C23255
5.1kΩ,"R4,R5",R_0402,C25905
75Ω,"R59,R60,R61,R62",R_0603,C4275
220kΩ,"R74,R76",R_0402,C25767
33Ω,"R10,R100,R11,R110,R88,R89,R90,R91,R92,R93,R94,R95,R96,R97,R98,R99",R_0402,C25105
H1102NLT,T1,H1102NLT_C18584,C18584
0Ω,"TST-R1,TST-R10,TST-R12,TST-R13,TST-R14,TST-R16,TST-R17,TST-R18,TST-R19,TST-R2,TST-R20,TST-R21,TST-R22,TST-R23,TST-R24,TST-R25,TST-R26,TST-R27,TST-R28,TST-R29,TST-R3,TST-R30,TST-R31,TST-R32,TST-R5,TST-R6,TST-R7,TST-R8,TST-R9",R_0603,C21189
TLV62568DBVR,U1,SOT-23-5,C163219
TM1637,U11,digital tube drivers_c2962580,C5337160
"LM75BDP,118",U12,TSSOP-8_3x3mm_P0.65mm,C33099
W25Q128JVSIQ,U13,SOIC-8_L5.3-W5.3-P1.27-LS8.0-BL,C97521
MAX98357AETE+T,U15,MAX98357AETE+T_C910544,C910544
MSM261DGT003,"U16,U17",LGA-6_2.0x4.0mm_MSM261DGT003,C48227730
AXP2101,U18,QFN-40-1EP_5x5mm_P0.4mm_EP3.6x3.6mm_ThermalVias,C3036461
DL-RFM95-915M,U19,RFM69HCW,C2844473
PCA9685PW,U20,TSSOP-28_4.4x9.7mm_P0.65mm,C2678753
TCA9555PWR,"U21,U22",TSSOP-24_4.4x7.8mm_P0.65mm,C465732
USBLC6-2SC6,U3,SOT-23-6,C2827654
XC6206-1.5NR,U5,SOT-23-3,C2984869
XC6206-2.8V,U6,SOT-23-3,C41424780
ESP32-S3,U7,QFN-56-1EP_7x7mm_P0.4mm_EP4x4mm_ThermalVias,C2913194
W5500,U9,LQFP-48_7x7mm_P0.5mm,C32843
X322525MOB4SI,X1,OSC-SMD_4P-L3.2-W2.5-BL,C9006
"40MHz, 15pF",Y1,OSC-SMD_4P-L3.2-W2.5-BL_SIT8008BI,C9010

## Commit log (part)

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2025-05-09 Initial draft commit. Non Functional.
2025-05-09 draft commit
2025-05-09 draft check in
2025-05-10 Draft commit, needs routing, schematic is probably mostly OK. Footprints are roughly located.
2025-05-22 draft commit, mostly added notes
2025-05-27 DRAFT added AXP2101 battery circuit
2025-05-28 DRAFT added misc outputs, PMU and resolved some TODO notes.
2025-05-30 DRAFT added mic jack.
2025-08-12 Draft Updated ESP32-S3 now includes 8MB internal PSRAM
2025-08-14 Draft Misc changes, layout still needs a lot of work.
2025-08-15 Draft misc layout, layout still needs a lot of work
2025-08-16 DRAFT commit, still needs lots of layout work.
2025-08-17 DRAFT commit, still needs lots of layout work. Everything connected, 70+ errors to resolve or ignore.
2025-08-18 Draft Commit, probably OK-ish. Lots of errors and warnings, but probably not important.
2025-08-24 DRAFT fixed many things with ANT1, added ANT2, moved MicJack to edge of PCB
2025-08-25 Added 1st spin files
2025-08-25 Added README.md
2025-08-26 DRAFT added smaller PCB design
2025-08-26 Draft smaller board.
2025-08-27 Draft
2025-08-27 Reverted Smaller
2025-08-27 Draft Medium
2025-08-28 Draft Medium re-annotated.
2025-08-29 Medium R0.1 production files created
2025-08-29 Updated name
2025-08-29 Added smaller production files.
2025-08-29 Changed Vdrive2 net from PMU.Vo1 to VDCDC5
2025-08-29 Changed input power from 3.3V to 5V.
2025-08-29 flipped RC servo headers to back side.
2025-09-02 Moved PCB edge to make easier to get SD card out.
2025-09-04 V0.1 updates added pictures and exported 3D file
2025-09-04 Updated PCB edge to allow easier access to SD card.
2025-09-04 updated smaller board layout
2025-12-02 Fix image paths in README for 3D pictures
2025-12-23 Added LORA module rough draft
2025-12-27 Draft commit added LORA
2026-01-19 Minor updates, looks like it's ready for 1st spin.
2026-01-19 added C107 to help with surge suppression
2026-01-20 Draft commit, added 33 ohms to camera lines to prevent cross talk
2026-06-14 updated to lower cost mic
2026-06-14 added mic.sck, mic.sd, and mic.ws term resistors
2026-06-14 moved nets off of conflicting psram IO.
2026-06-14 combined speaker and mic I2S signals making progress on IO count.
2026-06-14 re-connected digital signals now without conflict on PSRAM IO. Layout needs updating.
2026-06-14 updated pin out layout is now off of PSRAM IO.
2026-06-14 flipped D6 and D7 back to original pins, needed for internal connects.
